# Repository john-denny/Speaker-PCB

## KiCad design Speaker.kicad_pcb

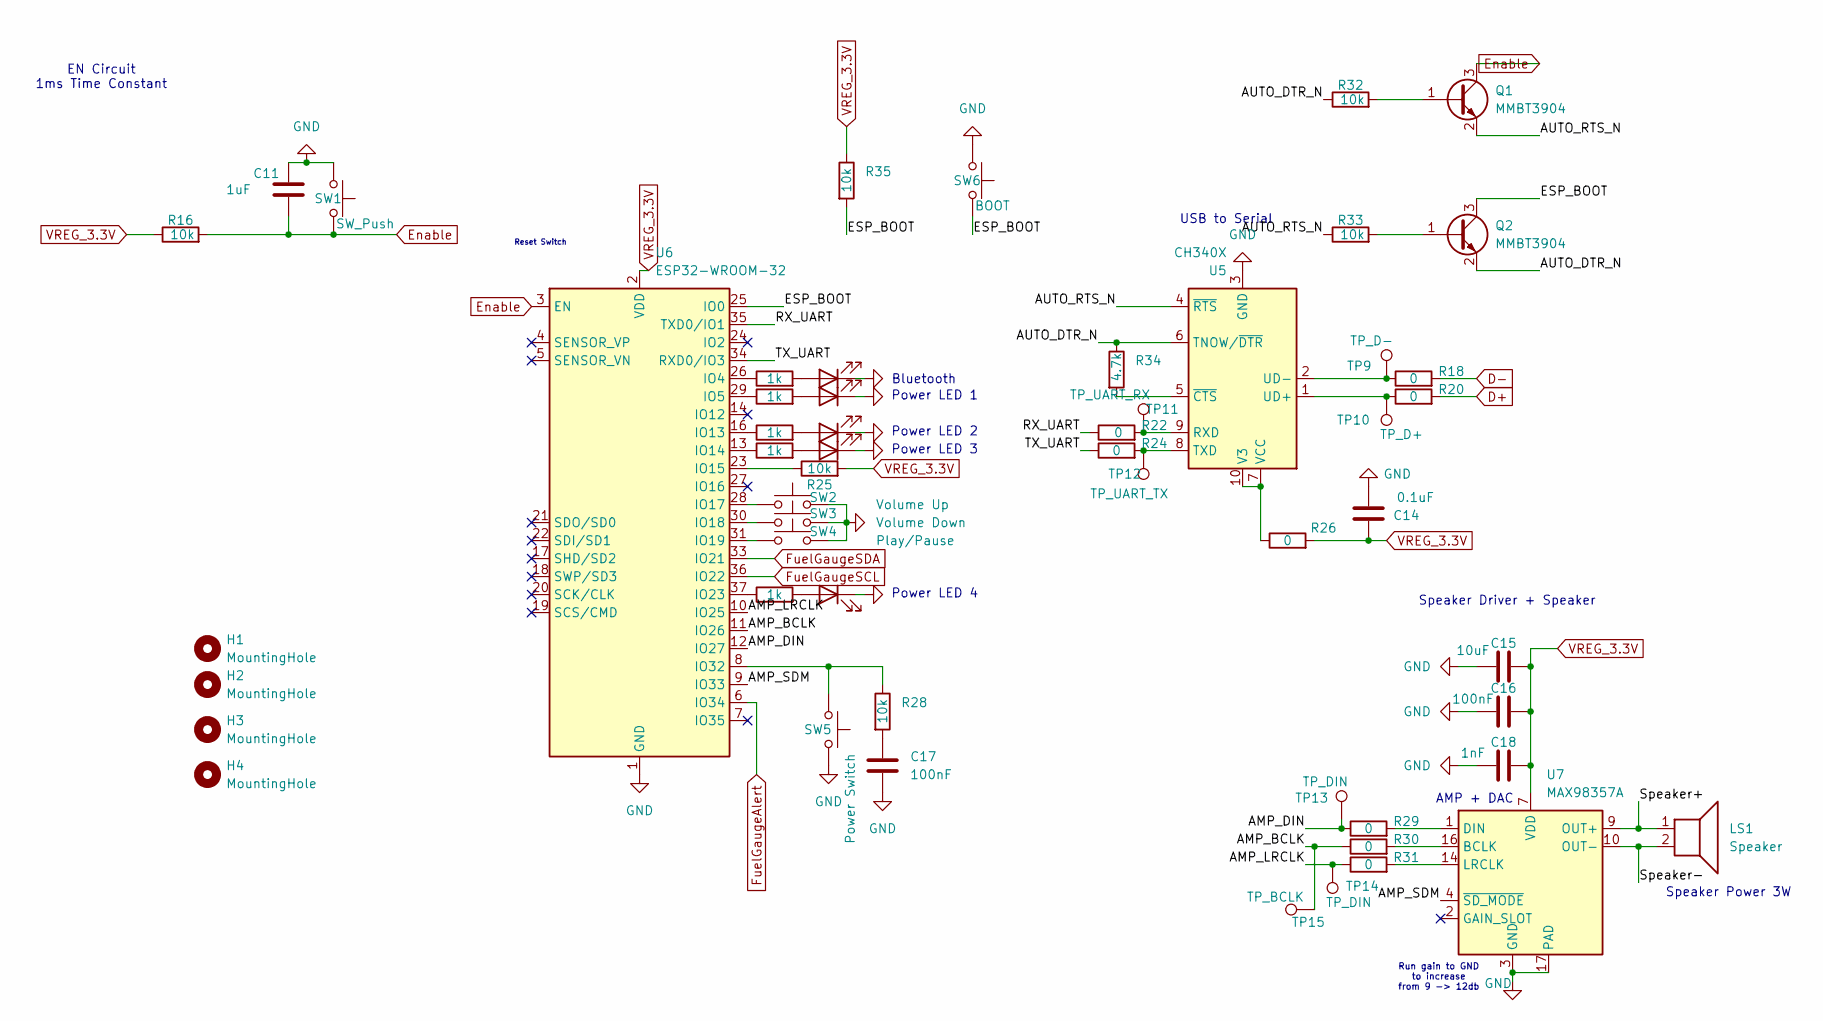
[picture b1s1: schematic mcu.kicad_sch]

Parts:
C11: 1uF; C_0603_1608Metric_Pad1.08x0.95mm_HandSolder; LCSC Part # C15849
C14: 0.1uF; C_0603_1608Metric_Pad1.08x0.95mm_HandSolder; LCSC Part # C14663
C15: 10uF; C_0603_1608Metric_Pad1.08x0.95mm_HandSolder; LCSC Part # C96446
C16, C17: 100nF; C_0603_1608Metric_Pad1.08x0.95mm_HandSolder; LCSC Part # C14663
C18: 1nF; C_0603_1608Metric_Pad1.08x0.95mm_HandSolder; LCSC Part # C1636
D3, D4, D5, D6, D7: LED; LED_0603_1608Metric_Pad1.05x0.95mm_HandSolder
H1, H2, H3, H4: MountingHole; MountingHole_2.2mm_M2_Pad_Via
LS1: Speaker; JST_PH_S2B-PH-K_1x02_P2.00mm_Horizontal
Q1, Q2: MMBT3904; SOT-23
R16, R25, R28, R32, R33, R35: 10k; R_0603_1608Metric_Pad0.98x0.95mm_HandSolder; LCSC Part # C25804
R17, R19, R21, R23, R27: 1k; R_0603_1608Metric_Pad0.98x0.95mm_HandSolder; LCSC Part # C21190
R18, R20, R22, R24, R26, R29, R30, R31: 0; R_0603_1608Metric_Pad0.98x0.95mm_HandSolder; LCSC Part # C21189
R34: 4.7k; R_0603_1608Metric_Pad0.98x0.95mm_HandSolder; LCSC Part # C23162
SW1: SW_Push; SW_SPST_B3U-1000P
SW2: Volume Up; SW_SPST_B3U-1000P
SW3: Volume Down; SW_SPST_B3U-1000P
SW4: Play/Pause; SW_SPST_B3U-1000P
SW5: Power Switch; SW_SPST_B3U-1000P
SW6: BOOT; SW_SPST_B3U-1000P
TP9: TP_D-; TestPoint_Pad_D1.5mm
TP10: TP_D+; TestPoint_Pad_D1.5mm
TP11: TP_UART_RX; TestPoint_Pad_D1.5mm
TP12: TP_UART_TX; TestPoint_Pad_D1.5mm
TP13, TP14: TP_DIN; TestPoint_Pad_D1.5mm
TP15: TP_BCLK; TestPoint_Pad_D1.5mm
U5: CH340X; MSOP-10_3x3mm_P0.5mm; LCSC Part # C3035748
U6: ESP32-WROOM-32; LCSC Part # C701342
U7: MAX98357A; TQFN-16-1EP_3x3mm_P0.5mm_EP1.23x1.23mm; LCSC Part # C910544

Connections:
/MCU/AMP_BCLK: R30.1, TP15.1, U6.11 (IO26)
/MCU/AMP_DIN: R29.1, TP13.1, U6.12 (IO27)
/MCU/AMP_LRCLK: R31.1, TP14.1, U6.10 (IO25)
/MCU/AMP_SDM: U6.9 (IO33), U7.4 (~SD_MODE)
/MCU/AUTO_DTR_N: Q2.2 (E), R32.1, R34.1, U5.6 (TNOW/~DTR)
/MCU/AUTO_RTS_N: Q1.2 (E), R33.1, U5.4 (~RTS)
/MCU/ESP_BOOT: Q2.3 (C), R35.2, SW6.2, U6.25 (IO0)
/MCU/RX_UART: R22.1, U6.35 (TXD0/IO1)
/MCU/Speaker+: LS1.1, U7.9 (OUT+)
/MCU/Speaker-: LS1.2, U7.10 (OUT-)
/MCU/TX_UART: R24.1, U6.34 (RXD0/IO3)
D+: R20.2; also elsewhere on the board
D-: R18.2; also elsewhere on the board
Enable: C11.2, Q1.3 (C), R16.2, SW1.2, U6.3 (EN)
FuelGaugeAlert: U6.6 (IO34); also elsewhere on the board
FuelGaugeSCL: U6.36 (IO22); also elsewhere on the board
FuelGaugeSDA: U6.33 (IO21); also elsewhere on the board
GND: C11.1, C14.1, C15.1, C16.1, C17.2, C18.1, D3.1 (K), D4.1 (K), D5.1 (K), D6.1 (K), D7.1 (K), SW1.1, SW2.2, SW3.2, SW4.2, SW5.2, SW6.1, U5.3 (GND), U6.1 (GND), U6.15 (GND), U6.38 (GND), U6.39 (GND), U7.3 (GND), U7.11 (GND), U7.15 (GND), U7.17 (PAD); also elsewhere on the board
unnamed: C17.1, R28.2
unnamed: D3.2 (A), R17.2
unnamed: D4.2 (A), R19.2
unnamed: D5.2 (A), R21.2
unnamed: D6.2 (A), R23.2
unnamed: D7.2 (A), R27.2
unnamed: Q1.1 (B), R32.2
unnamed: Q2.1 (B), R33.2
unnamed: R22.2, TP11.1, U5.9 (RXD)
unnamed: R24.2, TP12.1, U5.8 (TXD)
unnamed: R20.1, TP10.1, U5.1 (UD+)
unnamed: R18.1, TP9.1, U5.2 (UD-)
unnamed: R26.1, U5.7 (VCC), U5.10 (V3)
unnamed: R34.2, U5.5 (~CTS)
unnamed: R17.1, U6.26 (IO4)
unnamed: R19.1, U6.29 (IO5)
unnamed: R21.1, U6.16 (IO13)
unnamed: R23.1, U6.13 (IO14)
unnamed: R25.1, U6.23 (IO15)
unnamed: SW2.1, U6.28 (IO17)
unnamed: SW3.1, U6.30 (IO18)
unnamed: SW4.1, U6.31 (IO19)
unnamed: R27.1, U6.37 (IO23)
unnamed: R28.1, SW5.1, U6.8 (IO32)
unnamed: R30.2, U7.16 (BCLK)
unnamed: R29.2, U7.1 (DIN)
unnamed: R31.2, U7.14 (LRCLK)
VREG_3.3V: C14.2, C15.2, C16.2, C18.2, R16.1, R25.2, R26.2, R35.1, U6.2 (VDD), U7.7 (VDD), U7.8 (VDD); also elsewhere on the board

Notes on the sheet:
AMP + DAC
Reset Switch
Power LED 4
Bluetooth
EN Circuit 1ms Time Constant
Speaker Driver + Speaker
Power LED 3
USB to Serial
Speaker Power 3W
Run gain to GND to increase from 9 -> 12db
Power LED 2
Power LED 1

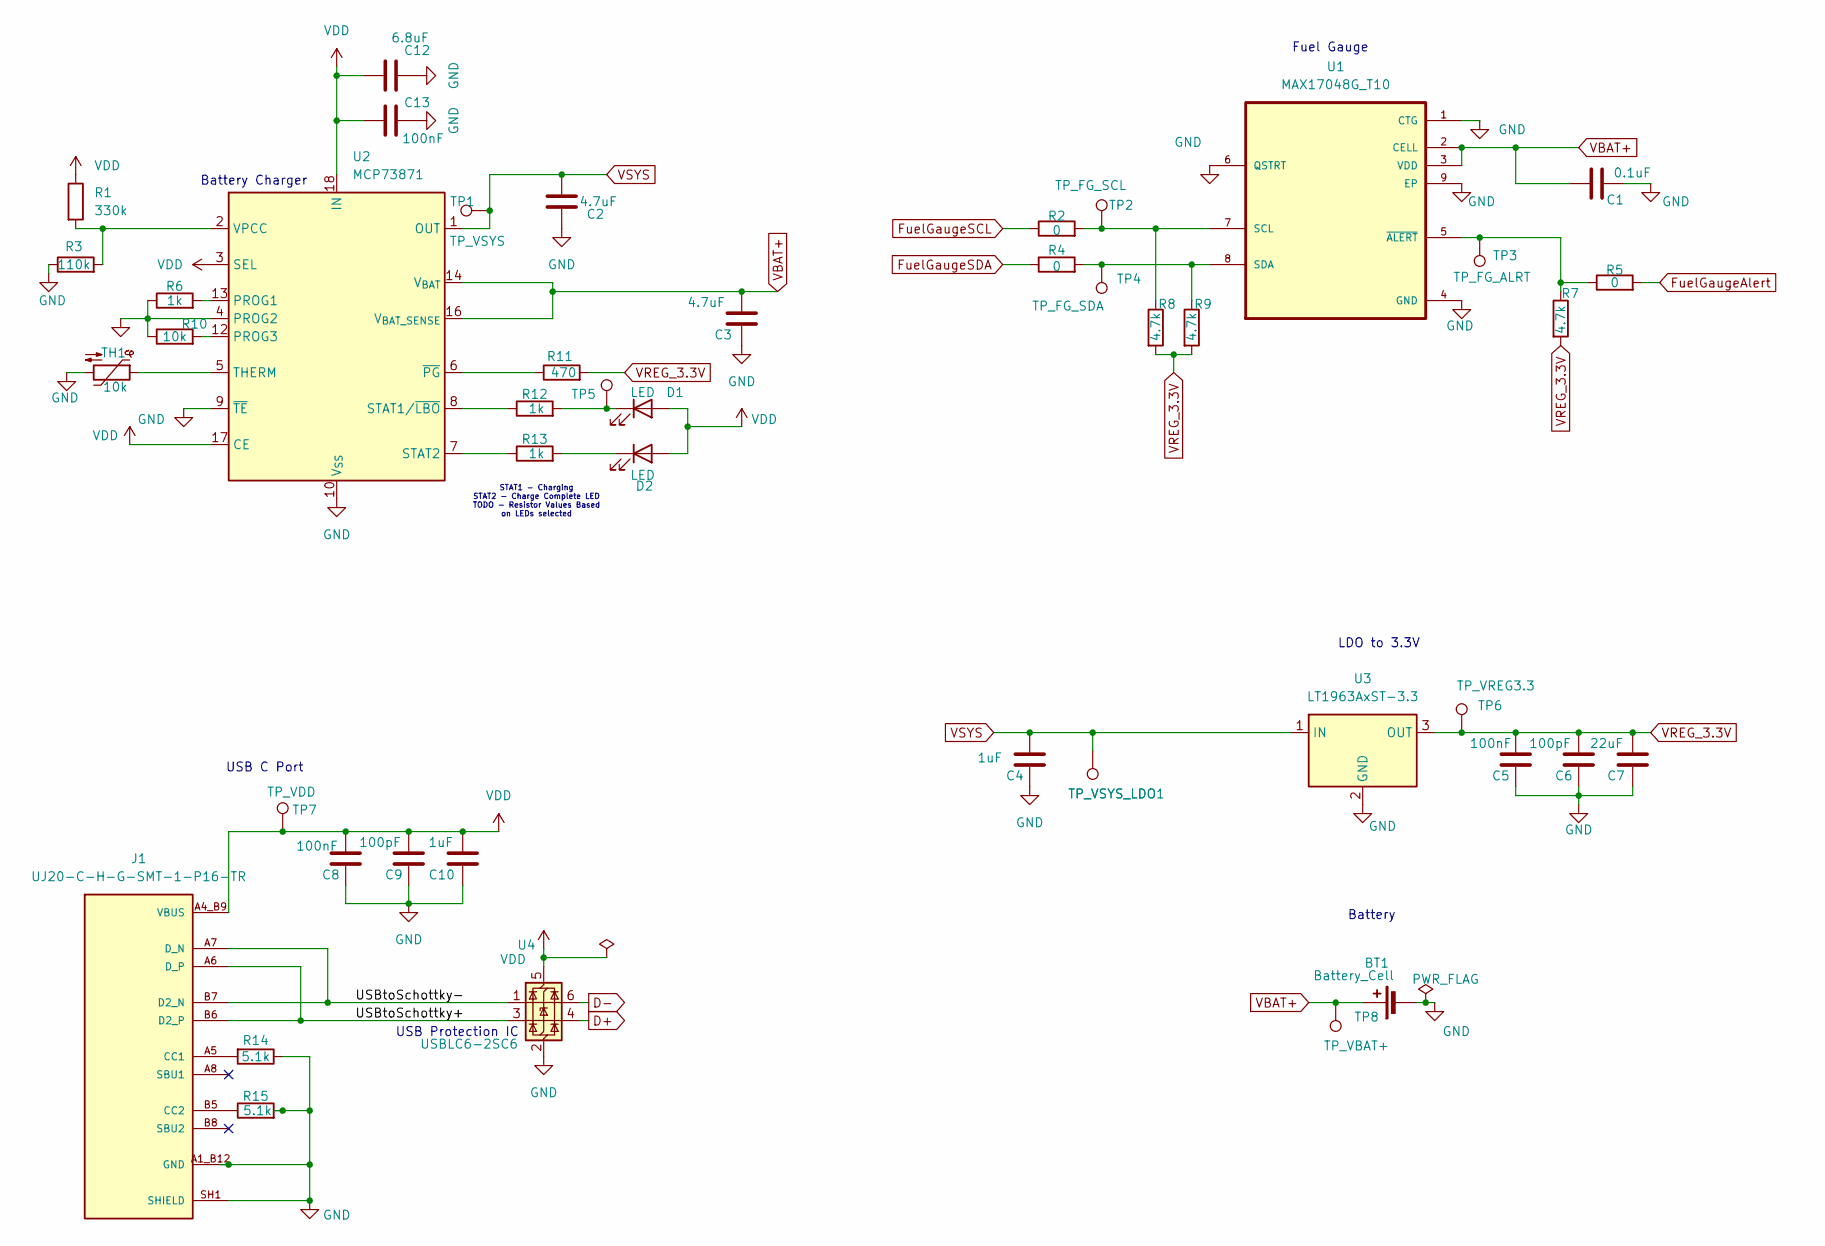
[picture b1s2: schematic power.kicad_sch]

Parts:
BT1: Battery_Cell; JST_PH_S2B-PH-K_1x02_P2.00mm_Horizontal
C1: 0.1uF; C_0603_1608Metric_Pad1.08x0.95mm_HandSolder; LCSC Part # C14663
C2, C3: 4.7uF; C_0603_1608Metric_Pad1.08x0.95mm_HandSolder; LCSC Part # C19666
C4, C10: 1uF; C_0603_1608Metric_Pad1.08x0.95mm_HandSolder; LCSC Part # C15849
C5, C8, C13: 100nF; C_0603_1608Metric_Pad1.08x0.95mm_HandSolder; LCSC Part # C14663
C6, C9: 100pF; C_0603_1608Metric_Pad1.08x0.95mm_HandSolder; LCSC Part # C14858
C7: 22uF; C_1206_3216Metric_Pad1.33x1.80mm_HandSolder; LCSC Part # C12891
C12: 6.8uF; C_1206_3216Metric_Pad1.33x1.80mm_HandSolder; LCSC Part # C2175442
D1, D2: LED; LED_0603_1608Metric_Pad1.05x0.95mm_HandSolder
J1: UJ20-C-H-G-SMT-1-P16-TR; SAMESKY_UJ20-C-H-G-SMT-1-P16-TR; PARTREV 1.0; LCSC Part # C45082766
R1: 330k; R_0603_1608Metric_Pad0.98x0.95mm_HandSolder; LCSC Part # C23137
R2, R4, R5: 0; R_0603_1608Metric_Pad0.98x0.95mm_HandSolder; LCSC Part # C21189
R3: 110k; R_0603_1608Metric_Pad0.98x0.95mm_HandSolder; LCSC Part # C123019
R6, R12, R13: 1k; R_0603_1608Metric_Pad0.98x0.95mm_HandSolder; LCSC Part # C21190
R7, R8, R9: 4.7k; R_0603_1608Metric_Pad0.98x0.95mm_HandSolder; LCSC Part # C23162
R10: 10k; R_0603_1608Metric_Pad0.98x0.95mm_HandSolder; LCSC Part # C25804
R11: 470; R_0603_1608Metric_Pad0.98x0.95mm_HandSolder; LCSC Part # C23179
R14, R15: 5.1k; R_0603_1608Metric_Pad0.98x0.95mm_HandSolder; LCSC Part # C23186
TH1: 10k; R_0603_1608Metric_Pad0.98x0.95mm_HandSolder; LCSC Part # C484775
TP1: TP_VSYS; TestPoint_Pad_D1.5mm
TP2: TP_FG_SCL; TestPoint_Pad_D1.5mm
TP3: TP_FG_ALRT; TestPoint_Pad_D1.5mm
TP4: TP_FG_SDA; TestPoint_Pad_D1.5mm
TP5: TP_Charging; TestPoint_Pad_D1.5mm
TP6: TP_VREG3.3; TestPoint_Pad_D1.5mm
TP7: TP_VDD; TestPoint_Pad_D1.5mm
TP8: TP_VBAT+; TestPoint_Pad_D1.5mm
TP_VSYS_LDO1: TP_VSYS_LDO; TestPoint_Pad_D1.5mm
U1: MAX17048G_T10; SON50P200X200X80-9N; LCSC Part # C2682616
U2: MCP73871; QFN-20-1EP_4x4mm_P0.5mm_EP2.5x2.5mm; LCSC Part # C511310
U3: LT1963AxST-3.3; SOT-223-3_TabPin2; LCSC Part # C117200
U4: USBLC6-2SC6; SOT-23-6; LCSC Part # C558442

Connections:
/Power/USBtoSchottky+: J1.A6 (D_P), J1.B6 (D2_P), U4.3 (I/O2)
/Power/USBtoSchottky-: J1.A7 (D_N), J1.B7 (D2_N), U4.1 (I/O1)
D+: U4.4 (I/O2); also elsewhere on the board
D-: U4.6 (I/O1); also elsewhere on the board
FuelGaugeAlert: R5.2; also elsewhere on the board
FuelGaugeSCL: R2.1; also elsewhere on the board
FuelGaugeSDA: R4.1; also elsewhere on the board
GND: BT1.2 (-), C1.2, C2.2, C3.2, C4.1, C5.1, C6.1, C7.1, C8.1, C9.1, C10.1, C12.2, C13.2, J1.A1_B12 (GND), J1.B1_A12 (GND), J1.SH1 (SHIELD), J1.SH2 (SHIELD), J1.SH3 (SHIELD), J1.SH4 (SHIELD), R3.1, R6.1, R10.1, R14.1, R15.2, TH1.2, U1.1 (CTG), U1.4 (GND), U1.6 (QSTRT), U1.9 (EP), U2.4 (PROG2), U2.9 (~TE), U2.10 (V_{SS}), U2.11 (V_{SS}), U2.21 (V_{SS}), U3.2 (GND), U4.2 (GND); also elsewhere on the board
unnamed: D1.1 (K), R12.2, TP5.1
unnamed: D2.1 (K), R13.2
unnamed: J1.A5 (CC1), R14.2
unnamed: J1.B5 (CC2), R15.1
unnamed: R2.2, R8.1, TP2.1, U1.7 (SCL)
unnamed: R4.2, R9.1, TP4.1, U1.8 (SDA)
unnamed: R5.1, R7.1, TP3.1, U1.5 (~ALERT)
unnamed: R6.2, U2.13 (PROG1)
unnamed: R10.2, U2.12 (PROG3)
unnamed: R12.1, U2.8 (STAT1/~LBO)
unnamed: R13.1, U2.7 (STAT2)
unnamed: TH1.1, U2.5 (THERM)
unnamed: R1.2, R3.2, U2.2 (VPCC)
unnamed: R11.1, U2.6 (~PG)
VBAT+: BT1.1 (+), C1.1, C3.1, TP8.1, U1.2 (CELL), U1.3 (VDD), U2.14 (V_{BAT}), U2.15 (V_{BAT}), U2.16 (V_{BAT_SENSE})
VDD: C8.2, C9.2, C10.2, C12.1, C13.1, D1.2 (A), D2.2 (A), J1.A4_B9 (VBUS), J1.B4_A9 (VBUS), R1.1, TP7.1, U2.3 (SEL), U2.17 (CE), U2.18 (IN), U2.19 (IN), U4.5 (VBUS)
VREG_3.3V: C5.2, C6.2, C7.2, R7.2, R8.2, R9.2, R11.2, TP6.1, U3.3 (OUT); also elsewhere on the board
VSYS: C2.1, C4.2, TP1.1, TP_VSYS_LDO1.1, U2.1 (OUT), U2.20 (OUT), U3.1 (IN)

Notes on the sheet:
LDO to 3.3V
Battery
USB C Port
USB Protection IC
Battery Charger
Fuel Gauge
STAT1 - Charging STAT2 - Charge Complete LED TODO - Resistor Values Based on LEDs selected

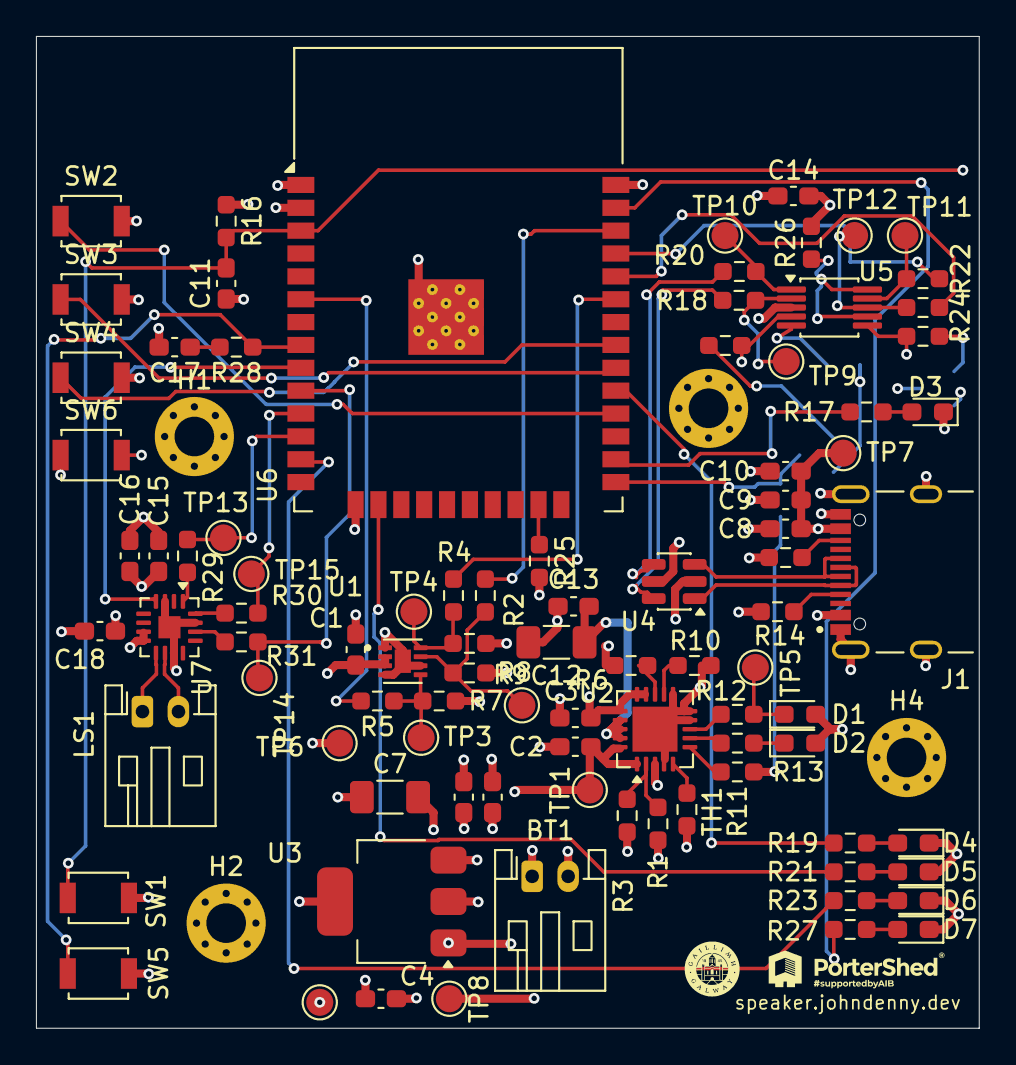
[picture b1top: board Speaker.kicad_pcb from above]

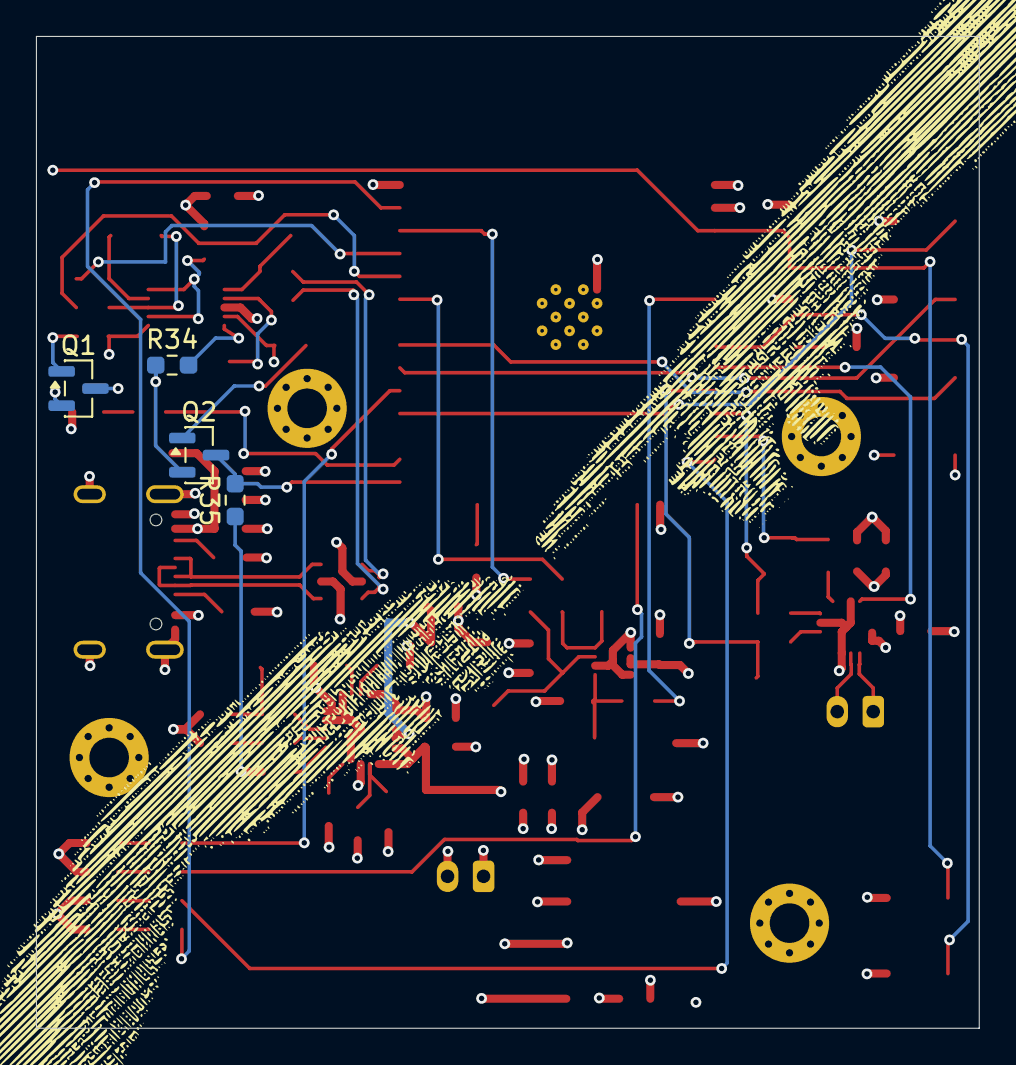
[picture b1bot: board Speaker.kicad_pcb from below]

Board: 4 copper layers, 52.4 x 55.1 mm, 99 parts (4 on the bottom side), 65 nets.

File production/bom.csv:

Designator,Footprint,Quantity,Value,LCSC Part #
BT1,JST_PH_S2B-PH-K_1x02_P2.00mm_Horizontal,1,Battery_Cell,
"C1, C14",0603,2,0.1uF,
"C10, C11, C4",0603,3,1uF,
C12,1206,1,6.8uF,
"C13, C16, C17, C5, C8",0603,5,100nF,
C15,0603,1,10uF,
C18,0603,1,1nF,
"C2, C3",0603,2,4.7uF,
"C6, C9",0603,2,100pF,
C7,1206,1,22uF,
"D1, D2, D3, D4, D5, D6, D7",0603,7,LED,
J1,SAMESKY_UJ20-C-H-G-SMT-1-P16-TR,1,UJ20-C-H-G-SMT-1-P16-TR,
LS1,JST_PH_S2B-PH-K_1x02_P2.00mm_Horizontal,1,Speaker,
"Q1, Q2",SOT-23,2,MMBT3904,
R1,0603,1,330k,
"R10, R16, R25, R28, R32, R33, R35, TH1",0603,8,10k,
R11,0603,1,470,
"R12, R13",0603,2,~,
"R14, R15",0603,2,5.1k,
"R17, R19, R21, R23, R27",0603,5,R,
"R18, R2, R20, R22, R24, R26, R29, R30, R31, R4, R5",0603,11,0,
R3,0603,1,110k,
"R34, R7, R8, R9",0603,4,4.7k,
R6,0603,1,1k,
SW1,SW_SPST_B3U-1000P,1,SW_Push,
SW2,SW_SPST_B3U-1000P,1,Volume Up,
SW3,SW_SPST_B3U-1000P,1,Volume Down,
SW4,SW_SPST_B3U-1000P,1,Play/Pause,
SW5,SW_SPST_B3U-1000P,1,Power Switch,
SW6,SW_SPST_B3U-1000P,1,BOOT,
TP1,TestPoint_Pad_D1.5mm,1,TP_VSYS,
TP10,TestPoint_Pad_D1.5mm,1,TP_D+,
TP11,TestPoint_Pad_D1.5mm,1,TP_UART_RX,
TP12,TestPoint_Pad_D1.5mm,1,TP_UART_TX,
"TP13, TP14",TestPoint_Pad_D1.5mm,2,TP_DIN,
TP15,TestPoint_Pad_D1.5mm,1,TP_BCLK,
TP2,TestPoint_Pad_D1.5mm,1,TP_FG_SCL,
TP3,TestPoint_Pad_D1.5mm,1,TP_FG_ALRT,
TP4,TestPoint_Pad_D1.5mm,1,TP_FG_SDA,
TP5,TestPoint_Pad_D1.5mm,1,TP_Charging,
TP6,TestPoint_Pad_D1.5mm,1,TP_VREG3.3,
TP7,TestPoint_Pad_D1.5mm,1,TP_VDD,
TP8,TestPoint_Pad_D1.5mm,1,TP_VBAT+,
TP9,TestPoint_Pad_D1.5mm,1,TP_D-,
TP_VSYS_LDO1,TestPoint_Pad_D1.5mm,1,TP_VSYS_LDO,
U1,SON50P200X200X80-9N,1,MAX17048G_T10,
U2,QFN-20-1EP_4x4mm_P0.5mm_EP2.5x2.5mm,1,MCP73871,
U3,SOT-223-3_TabPin2,1,LT1963AxST-3.3,
U4,SOT-23-6,1,USBLC6-2SC6,
U5,MSOP-10_3x3mm_P0.5mm,1,CH340X,
U6,ESP32-WROOM-32,1,ESP32-WROOM-32,
U7,TQFN-16-1EP_3x3mm_P0.5mm_EP1.23x1.23mm,1,MAX98357A,
